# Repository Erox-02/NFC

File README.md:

# NFC

A basic nfc card with custom antenna .

## Design 

The integrated planar antenna harvests power from the phone's magnetic field to  light up the led placed in front side pcb layer while simltaniously doing nfc connection with phone/other device . Also i have left some traces for later i2c uses .

### Back 

### Front

## How to make your own pcb?

Check out my project's build video's on forge 

[Forge](https://forge.hackclub.com/projects/2851)

you can re use my antenna and add custom footprint for others , or you can swap my name and qr with your own :D .

## Building The nfc  

I will use pcba on jlc pcb to order it because the parts are kinda rare in india and if i order frm lcsc , it will cost me more for shipping and moq .

But if you wanna solder/rework on your own , order the parts frm given links in bom and solder the components on the designated places as cpl.xlsx says , then connect the card with your nfc enabled phone and bind a url . Or you can use a esp 32/other mpu and rewrite the eeprom with i2c , **REMINDER : USE 2.2-3v POWER SUPPLY **

detailed steps for non pcba :

- Order the components listed in the bom.
- Place the components according to the xlsx file(use jlcpcb's pcba tool to mark things up with the cpl ).
- Solder the components onto the pcb.
- Bring the completed card near an nfc phone.
- Configure the ic with the  data.

The antenna is supposed to harvest energy from the nfc field,
which is more than enough to power the led while the nfc ic communicates
with the phone or whatever nfc device youre using.

## Credits 

- > [LINK]{https://neurotech-hub.github.io/KiCad-Antenna-Generator/}

- Kicad

## Author 

me , mineself Erox aka Dipanjan  

# BOM 

| Designator | Comment | Footprint | Quantity | LCSC Part # | LCSC Link | Unit Price |
|---|---|---|---:|---|---|---:|
| Cap1 | 180 nf | Capacitor_SMD:C_0603_1608Metric | 1 | C519440 | https://www.lcsc.com/product-detail/C519440.html | $0.0114 |
| D1 | LED | LED_0603_1608Metric | 1 | C19171394 | https://www.lcsc.com/product-detail/C19171394.html | See LCSC |
| R1 | 5k ohm | Resistor_SMD:R_0603_1608Metric | 1 | C862232 | https://www.lcsc.com/product-detail/Chip-Resistor-Surface-Mount_YAGEO-RT0603BRE075KL_C862232.html | $0.0293 |
| R2 | 5k ohm | Resistor_SMD:R_0603_1608Metric | 1 | C862232 | https://www.lcsc.com/product-detail/Chip-Resistor-Surface-Mount_YAGEO-RT0603BRE075KL_C862232.html | $0.0293 |
| R3 | 5k ohm | Resistor_SMD:R_0603_1608Metric | 1 | C862232 | https://www.lcsc.com/product-detail/Chip-Resistor-Surface-Mount_YAGEO-RT0603BRE075KL_C862232.html | $0.0293 |
| U1 | NT3H2111W0FHKH | XQFN-8_L1.6-W1.6-P0.50-BL_NT3H2111W0FHKH | 1 | C710403 | https://www.lcsc.com/product-detail/NFC-RFID-Tags_NXP-Semiconductors-NT3H2111W0FHKH_C710403.html | $0.6224 |

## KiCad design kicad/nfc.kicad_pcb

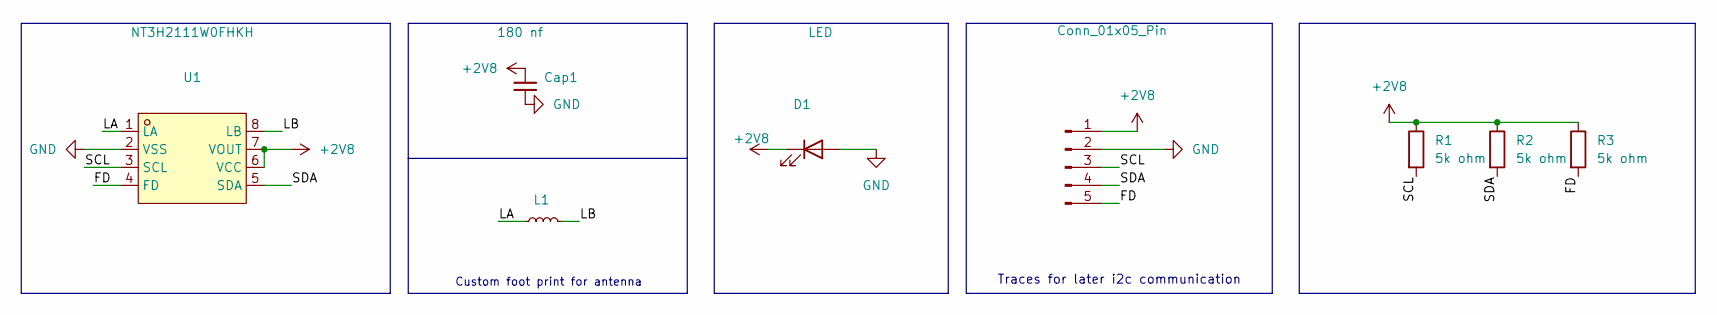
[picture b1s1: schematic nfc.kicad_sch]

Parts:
Cap1: 180 nf; C_0603_1608Metric
Con1: Conn_01x05_Pin; Hirose_DF13-05P-1.25DSA_1x05_P1.25mm_Vertical
D1: LED; LED_0603_1608Metric
L1: L_Small; ftprnt
R1, R2, R3: 5k ohm; R_0603_1608Metric
U1: NT3H2111W0FHKH; XQFN-8_L1.6-W1.6-P0.50-BL_NT3H2111W0FHKH; MPN NT3H2111W0FHKH; LCSC Part C710403

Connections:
+2V8: Cap1.1, Con1.1, D1.1 (K), R1.1, R2.1, R3.1, U1.6 (VCC), U1.7 (VOUT)
/FD: Con1.5, R3.2, U1.4 (FD)
/LA: L1.1, U1.1 (LA)
/LB: L1.2, U1.8 (LB)
/SCL: Con1.3, R1.2, U1.3 (SCL)
/SDA: Con1.4, R2.2, U1.5 (SDA)
GND: Cap1.2, Con1.2, D1.2 (A), U1.2 (VSS)

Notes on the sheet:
Traces for later i2c communication
Custom foot print for antenna

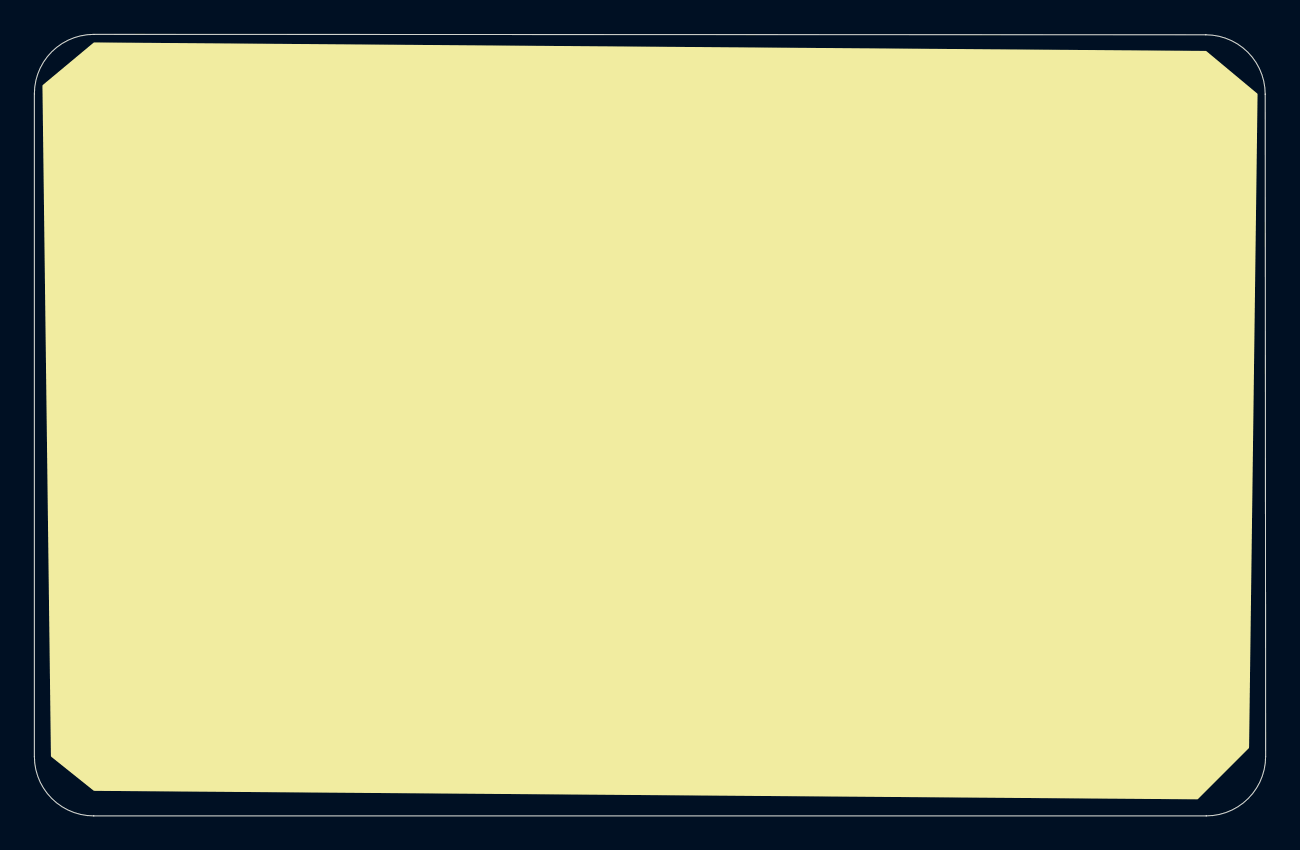
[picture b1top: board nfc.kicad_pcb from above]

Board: 2 copper layers, 72.6 x 46.1 mm, 8 parts (0 on the bottom side), 7 nets.

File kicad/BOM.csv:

"Reference","Qty","Value","DNP","Exclude from BOM","Exclude from Board","Exclude from Simulation","Exclude from Position Files","Footprint","Datasheet"
"Cap1","1","180 nf","","","","","${EXCLUDE_FROM_POS_FILES}","Capacitor_SMD:C_0402_1005Metric",""
"Con1","1","Conn_01x05_Pin","","","","","${EXCLUDE_FROM_POS_FILES}","Connector_Hirose:Hirose_DF13-05P-1.25DSA_1x05_P1.25mm_Vertical",""
"D1","1","LED","","","","","${EXCLUDE_FROM_POS_FILES}","LED_SMD:LED_0603_1608Metric",""
"R1,R2,R3","3","5k ohm","","","","","${EXCLUDE_FROM_POS_FILES}","Resistor_SMD:R_0402_1005Metric",""
"U1","1","NT3H2111W0FHKH","","","","","${EXCLUDE_FROM_POS_FILES}","easyeda2kicad:XQFN-8_L1.6-W1.6-P0.50-BL_NT3H2111W0FHKH","https://www.lcsc.com/datasheet/C710403.pdf"
